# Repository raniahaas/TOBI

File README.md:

# TOBI
Telemetry, Orientation and Barometric Instrument Flight Computer used for the University of Cincinnati's Rocketry Club's Projects.\

# Introduction
TOBI, from the Japanese word 飛び（とび「tobi」）meaning to soar, was born to serve as a custom avionics bay as a foundation for the University of Cincinnati's Rocketry Club's future space attempt, as well as a custom device personally. The overall goal for final development is to have a working custom flight computer that can log data, determine events, and fire pyrotechniques, all independently.

This repository is still in _**active development**_, but is intended as a clean starting ground to learn, teach, and develop further knowledge of avionics. 

| Goals | Method(s) of Execution |
| ------------- | ------------- |
| Multithreading | Using FreeRTOS, use the two cores on the ESP32-S3 to monitor and log events while another core stores data. This became a notable issue in past iterations where often data was missed, overlapped, or entirely logged improperly. |
| Event Logging | More specifically, events for apogee, main and drogue deployment, second-stage ignition, launch, and landing. |
| Pyrotechnics | Simulate the ignition of the second stage, wire cutters, and parachute deployment that current prefab electronics for model rocketry execute. This will become a full feature later on in the following year. |
| Wi-Fi Integration | Mostly, the ESP32 is known for its Wi-Fi capabilities. In our case, I will be utilising the Wi-Fi for data transfer and to check sensor continuity. This will be the main interface that the user uses to communicate with the device externally to the development. |
| Redundancy | Logging the sensors for data and comparing their redundancy with other computers or often COTS components to ensure our code is always performing to the best of its ability while also being the best option financially and methodologically.|

## Project Structure
```
tobiru/
├── data/
│   └── assets/          
│       └── TOBI_Logo.png
├── include/
│   └── flightState.h      # Hardware headers for the flight state
├── lib/                   # Project-specific libraries
├── src/
│   ├── startup/            
|       └── imu_init.cpp   # Initialise IMU datarates
|       └── imu_init.h
|       └── startupSeq.cpp # Start device and initialise accelerometer and barometer datarates; battery voltages
|       └── startupSeq.h
│   ├── globals.h          # Global elements
|   ├── globals.cpp
│   ├── main.cpp           # Task creations
│   └── wifiSetup.h        # Web dashboard with the Wi-Fi interface
├── test/                  # Unity test suites
│   ├── test_flightstate/
|       └── test_main.cpp
│   └── test_telemetry/
|       └── test_main.cpp
└── platformio.ini
```

## Device
| Insturment | Name |
| ---------- | ---- |
| Accelerometer | [Adafruit LSM6DSO32](https://www.digikey.com/en/products/detail/adafruit-industries-llc/4692/13250946) |
| Microcontroller | [XIAO SEEED ESP32-S3](https://www.digikey.com/en/products/detail/seeed-technology-co-ltd/113991114/19285530) |
| Barometer | [TE MS5611](https://www.digikey.com/en/products/detail/te-connectivity-measurement-specialties/MS561101BA03-50/5277445) |
| PCB | See KiCAD Files |
| Mosfet | [Toshiba T2N7002](https://www.digikey.com/en/products/detail/toshiba-semiconductor-and-storage/T2N7002BK-LM/5409245) |
| Additional elements | Battery terminal, 2-prong screw terminal, 4-prong screw terminal, resistors & transistors | 

## Project Status
- [X] Create multithreaded code for sensor logging (FreeRTOS)
- [X] Have a flight state machine for pre-launch, launch, and landing
- [X] Test functions before final implementation (Unity)
- [X] Local Wi-Fi server for live telemetry data and downloading post-flight data
- [X] PCB integration testing
- [ ] Use pyrotechniques for deploying main and drogue chutes
- [ ] Test flights!

## Building and Flashing Device
The native PlatformIO extension allows the user to flash to the device by simply validating the code and 'pushing' it onto the device. 

You can additionally flash the code manually by:
```
# Build and upload firmware to the flight computer
pio run -e esp32s3 -t upload

# Open serial monitor
pio device monitor
```

## Flight State
There are three main flight states: startup, ready, and landing. Startup occurs as soon as the device is powered on and will switch to ready once all checks are complete. In the ready state, the user on the front-end server can arm and disarm the device to start recording instruments for flight. Once events are detected and landing has been determined, the device will enter landing mode and produce summary information as well as downloads for CSV files for the user. 

| State | Description |
| ----- | ----------- |
| startup |	Sensor initialization runs (runStartupSequence()), Wi-Fi starts up |
|ready |	Initialisation complete, device idle, user can access webpage |
| armed	| Event detection is live — launch/apogee/landing checks run every cycle in shutDown()|
| landed	| Landing confirmed; event detection stops, flight summary data is finalised|

Transitions are currently one-directional (no state is re-entered), driven by main.cpp on startup/arm and by the event detection logic on landing confirmation.

## Flight Events
Key flight events are detected by a pure, hardware-independent function (updateFlightState), so the same logic that flies on the device can also be validated on a laptop with no board attached.

| Event | Trigger Condition |
| ----- | ----------------- |
|Launch |	Z-axis acceleration exceeds a threshold (~15 m/s²)|
|Motor Burnout | Gs drop and at least 0.5s have passed |
|Apogee |	Altitude drops more than 50m below the recorded peak|
|Landing | Altitude returns near launch altitude, acceleration stabilises near 1G, device is stable for 3+ seconds|

## Testing
Testing is natively done with the combination of PlatformIO and Unity, where instruments are stripped, and logic functions are tested. Flight-critical logic (launch detection, apogee confirmation, landing verification) is extracted into pure, hardware-independent functions.

```
pio test -e native -f test_flightstate
```
platformio.ini defines two environments inside of testing:
- esp32s3: the physical hardware board the main code runs off of
- native: emulates real hardware to test functions purely

## Safety
This project is intended for use in HPR (high-powered rocketry) and uses pyrotechniques to deploy parachutes and allow for second-stage ignitions. All safety protocols must follow NAR safety codes and are built in accordance with a recoverable HPR two-stage flight. Do not fire, wire, or test pyrotechnic channels without knowledge of the code, device, and user-controlled testing deployment.

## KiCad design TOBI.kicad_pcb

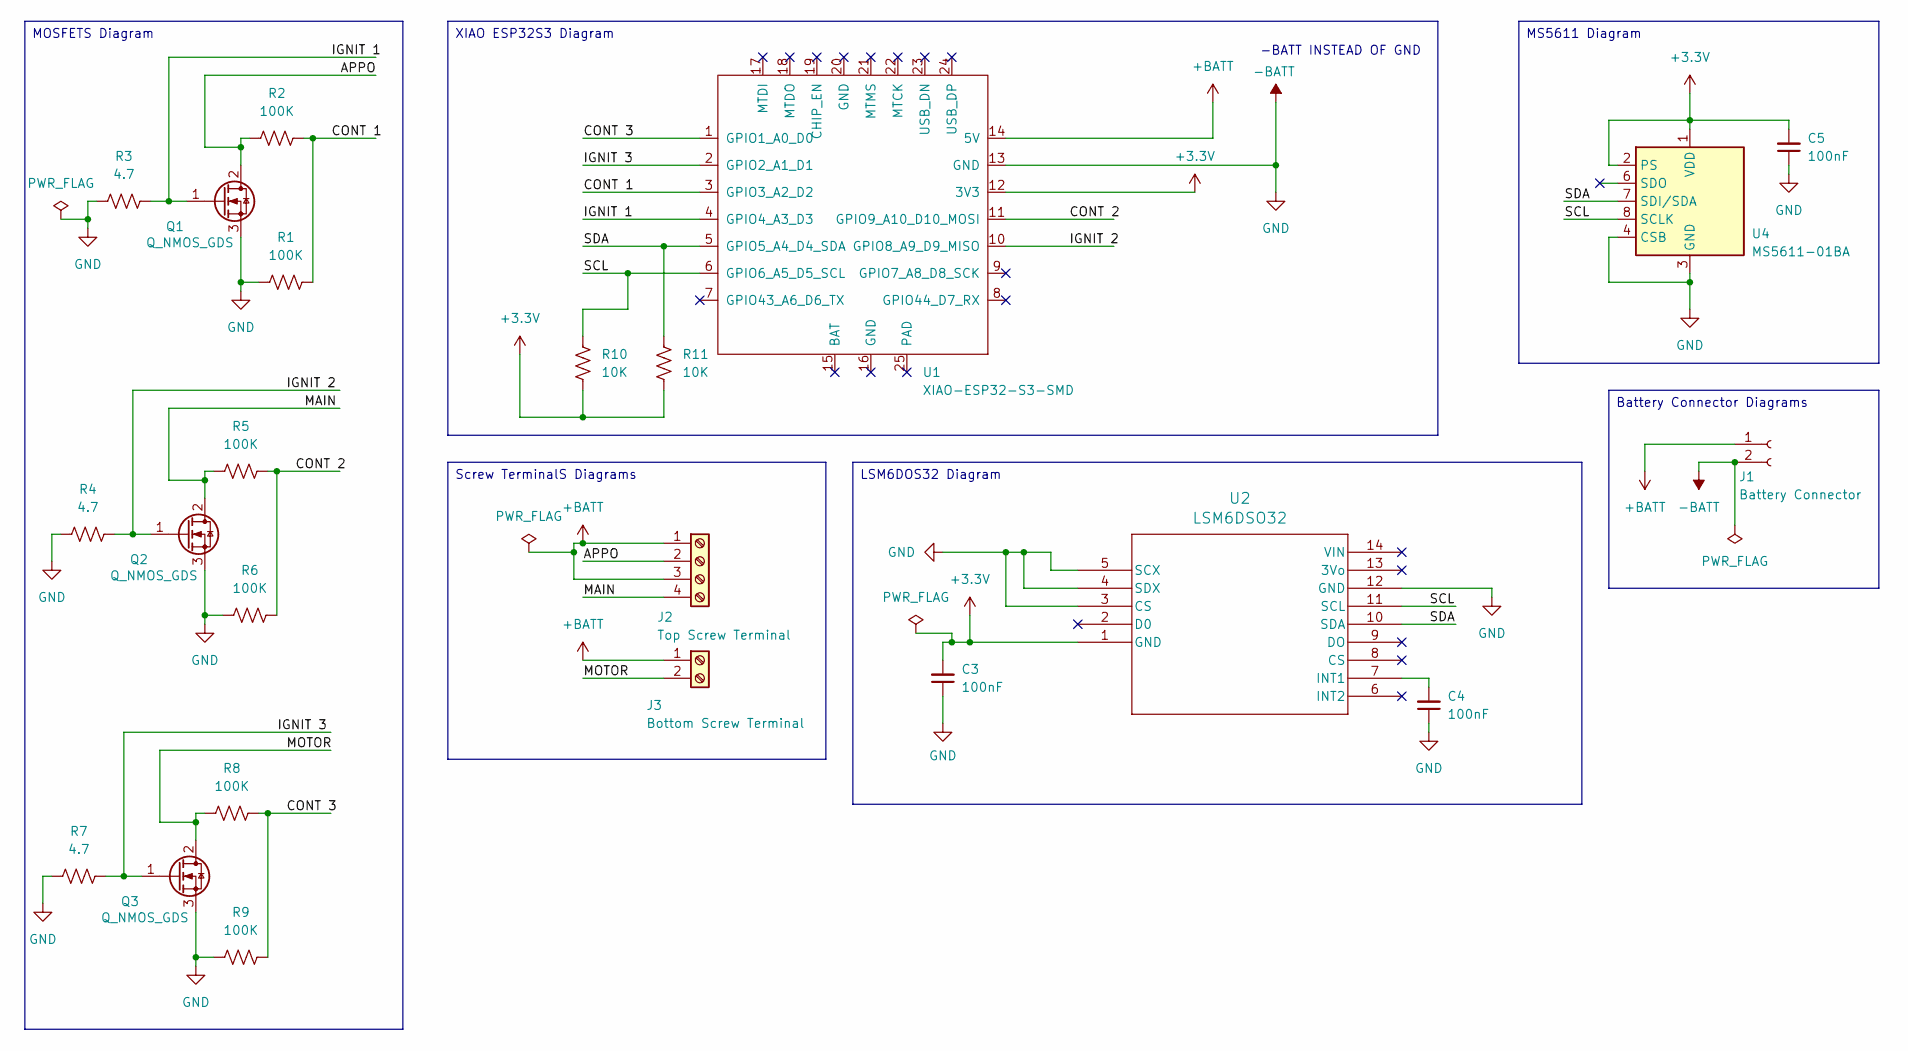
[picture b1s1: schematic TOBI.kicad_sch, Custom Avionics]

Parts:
C3, C4, C5: 100nF; C_0603_1608Metric
J1: Battery Connector; JST_PH_B2B-PH-K_1x02_P2.00mm_Vertical
J2: Top Screw Terminal; TerminalBlock_Phoenix_MPT-0,5-4-2.54_1x04_P2.54mm_Horizontal
J3: Bottom Screw Terminal; TerminalBlock_Phoenix_MPT-0,5-2-2.54_1x02_P2.54mm_Horizontal
Q1, Q2, Q3: Q_NMOS_GDS; SOT23_TOS
R1, R2, R5, R6, R8, R9: 100K; R_01005_0402Metric
R3, R4, R7: 4.7; R_01005_0402Metric
R10, R11: 10K; R_01005_0402Metric
U1: XIAO-ESP32-S3-SMD; XIAO-ESP32-S3-DIP
U2: LSM6DSO32
U4: MS5611-01BA; LGA-8_3x5mm_P1.25mm

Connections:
+3.3V: C3.2, C5.2, R10.1, R11.1, U1.12 (3V3), U2.1 (GND), U4.1 (VDD), U4.2 (PS)
+BATT: J1.1, J2.1, J2.3, J3.1, U1.14 (5V); also elsewhere on the board
-BATT: C3.1, C4.1, C5.1, J1.2, Q1.3 (S), Q2.3 (S), Q3.3 (S), R1.1, R3.1, R4.1, R6.1, R7.1, R9.1, U1.13 (GND), U2.3 (CS), U2.4 (SDX), U2.5 (SCX), U2.12 (GND), U4.3 (GND), U4.4 (CSB), U4.5 (CSB)
/APPO: J2.2, Q1.2 (D), R2.1
/CONT 1: R1.2, R2.2, U1.3 (GPIO3_A2_D2)
/CONT 2: R5.2, R6.2, U1.11 (GPIO9_A10_D10_MOSI)
/CONT 3: R8.2, R9.2, U1.1 (GPIO1_A0_D0)
/IGNIT 1: Q1.1 (G), R3.2, U1.4 (GPIO4_A3_D3)
/IGNIT 2: Q2.1 (G), R4.2, U1.10 (GPIO8_A9_D9_MISO)
/IGNIT 3: Q3.1 (G), R7.2, U1.2 (GPIO2_A1_D1)
/MAIN: J2.4, Q2.2 (D), R5.1
/MOTOR: J3.2, Q3.2 (D), R8.1; also elsewhere on the board
/SCL: R10.2, U1.6 (GPIO6_A5_D5_SCL), U2.11 (SCL), U4.8 (SCLK)
/SDA: R11.2, U1.5 (GPIO5_A4_D4_SDA), U2.10 (SDA), U4.7 (SDI/SDA)
unnamed: C4.2, U2.7 (INT1)

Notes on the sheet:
-BATT INSTEAD OF GND
XIAO ESP32S3 Diagram
MS5611 Diagram
MOSFETS Diagram
Screw TerminalS Diagrams
LSM6DOS32 Diagram
Battery Connector Diagrams

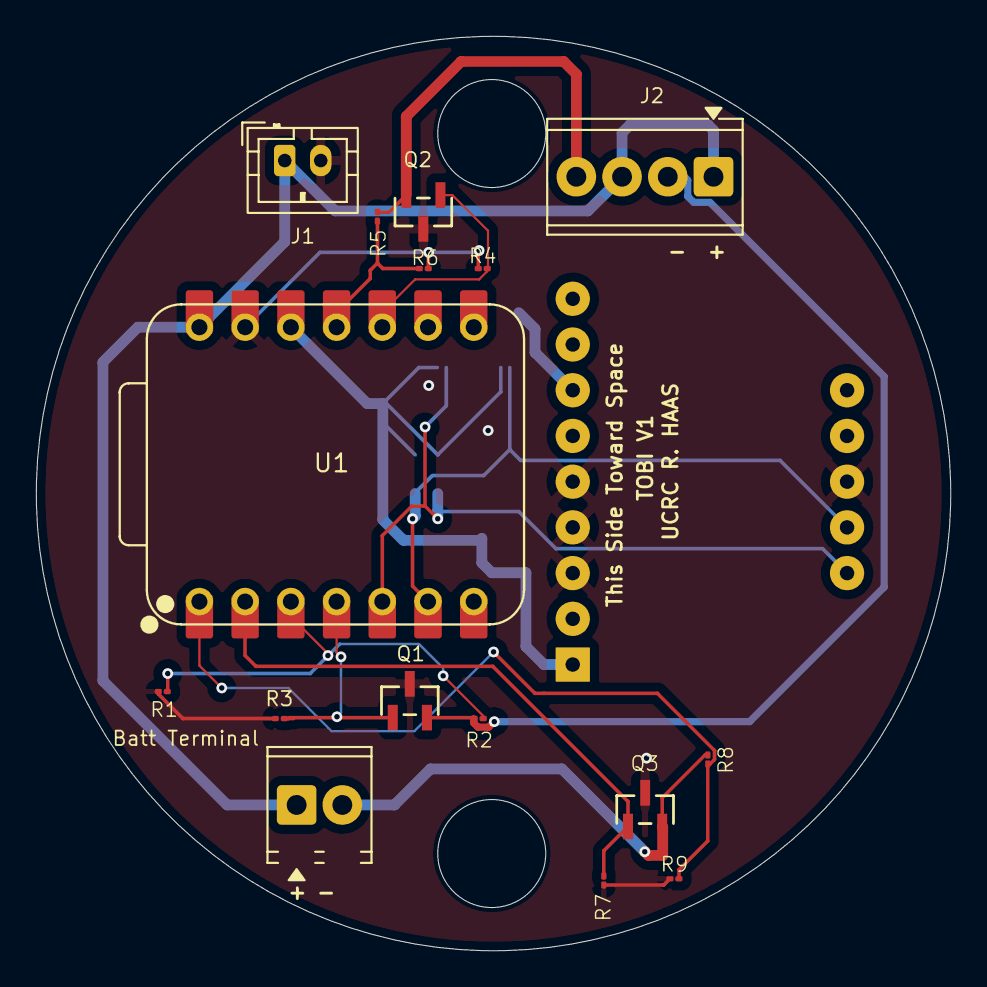
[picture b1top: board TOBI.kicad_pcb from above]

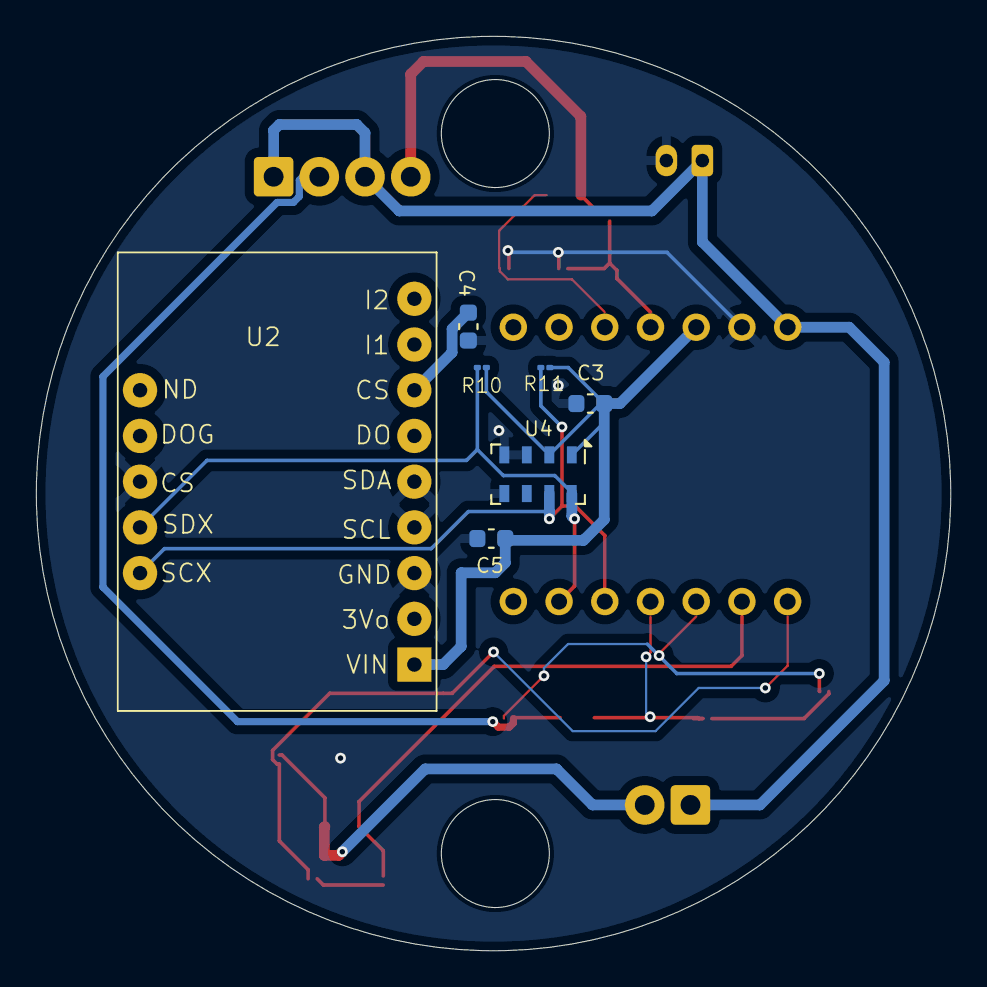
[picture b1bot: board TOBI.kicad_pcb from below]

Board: 4 copper layers, 50.8 x 50.8 mm, 23 parts (7 on the bottom side), 15 nets.

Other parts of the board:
Batt Terminal: Bottom Screw Terminal; TerminalBlock_Phoenix_MPT-0,5-2-2.54_1x02_P2.54mm_Horizontal

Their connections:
+BATT: Batt Terminal.1; also elsewhere on the board
/MOTOR: Batt Terminal.2; also elsewhere on the board

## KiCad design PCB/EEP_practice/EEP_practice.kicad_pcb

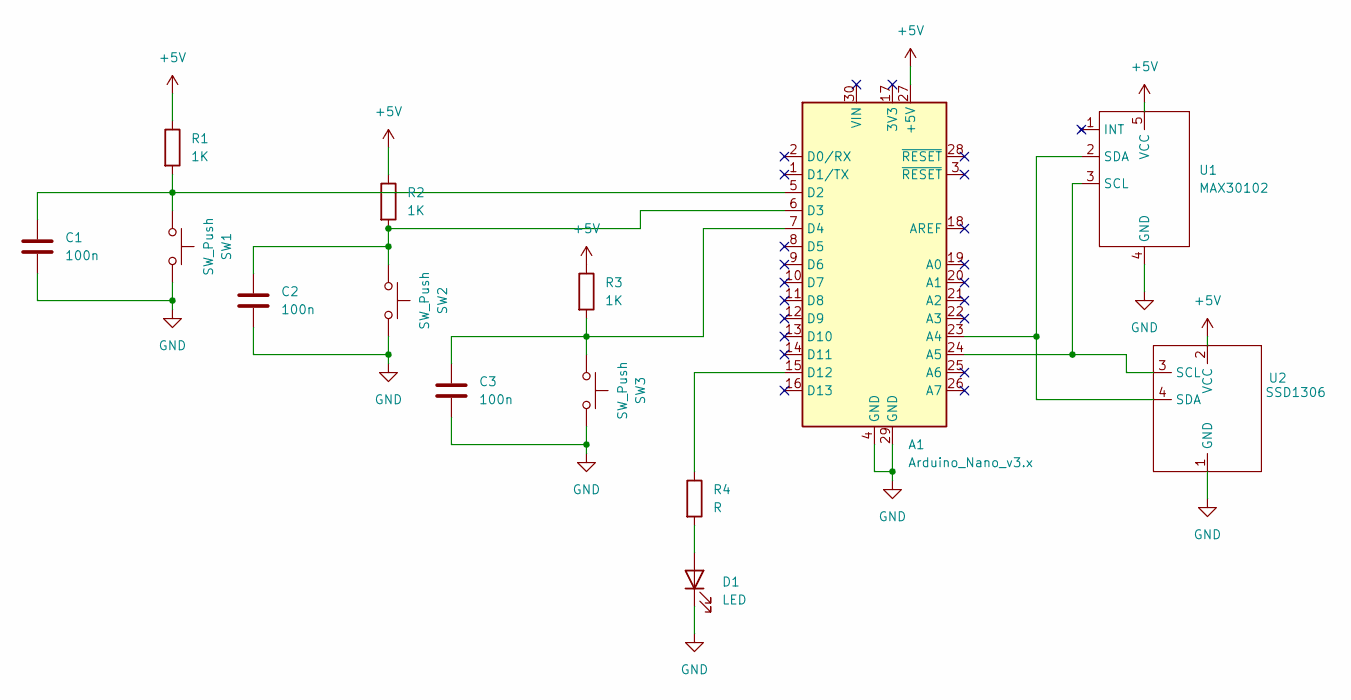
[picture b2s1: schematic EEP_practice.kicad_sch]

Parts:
A1: Arduino_Nano_v3.x; Arduino_Nano
C1, C2, C3: 100n; C_Disc_D4.7mm_W2.5mm_P5.00mm
D1: LED; LED_D5.0mm
R1, R2, R3: 1K; R_Axial_DIN0207_L6.3mm_D2.5mm_P15.24mm_Horizontal
R4: R; R_Axial_DIN0207_L6.3mm_D2.5mm_P15.24mm_Horizontal
SW1, SW2, SW3: SW_Push; SW_PUSH_6mm
U1: MAX30102; MAX30102_MODULE
U2: SSD1306

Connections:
+5V: A1.27 (+5V), R1.1, R2.1, R3.1, U1.5 (VCC), U2.2 (VCC)
GND: A1.4 (GND), A1.29 (GND), C1.2, C2.2, C3.2, D1.1 (K), SW1.2, SW2.2, SW3.2, U1.4 (GND), U2.1 (GND)
unnamed: A1.23 (A4), U1.2 (SDA), U2.4 (SDA)
unnamed: A1.24 (A5), U1.3 (SCL), U2.3 (SCL)
unnamed: A1.5 (D2), C1.1, R1.2, SW1.1
unnamed: A1.6 (D3), C2.1, R2.2, SW2.1
unnamed: A1.7 (D4), C3.1, R3.2, SW3.1
unnamed: A1.15 (D12), R4.1
unnamed: D1.2 (A), R4.2

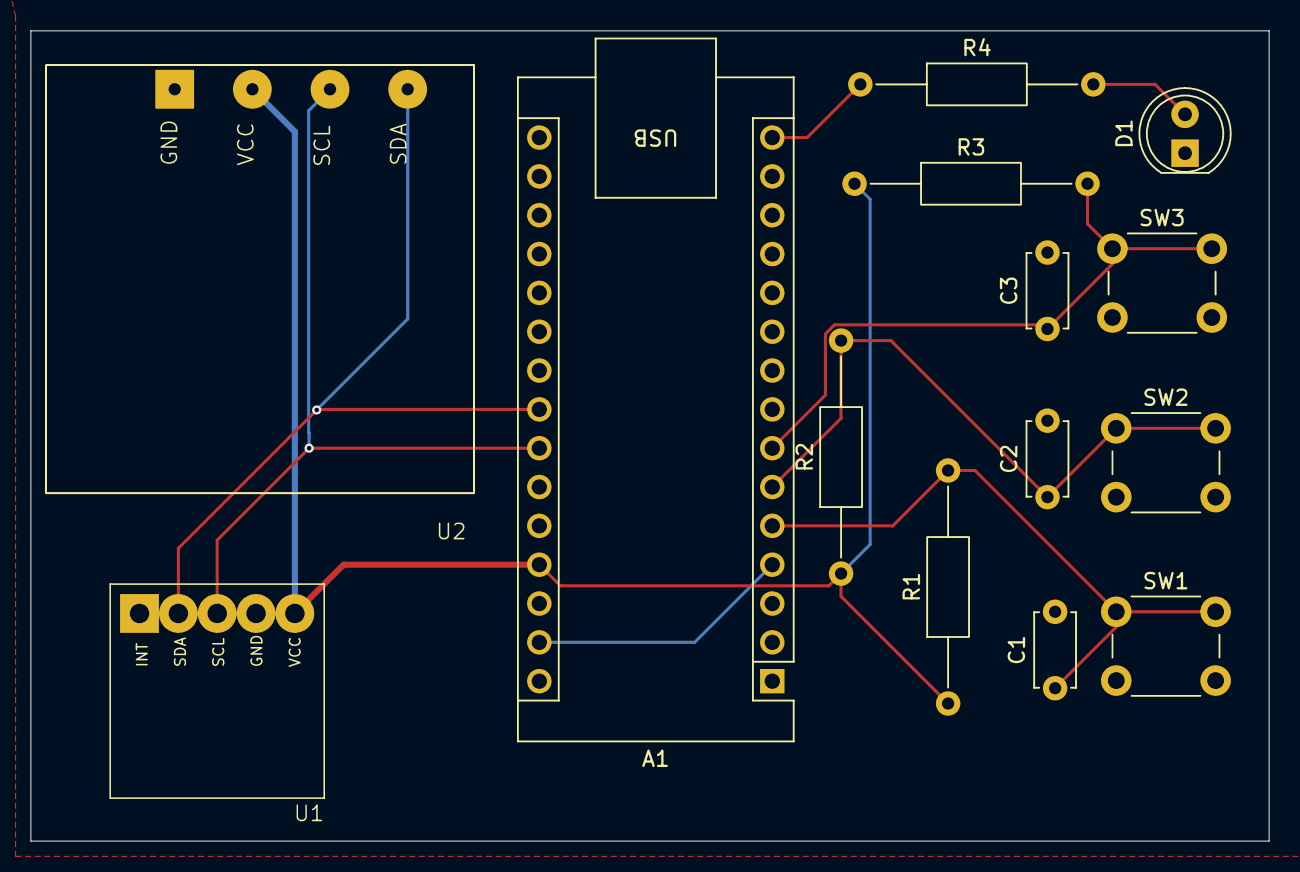
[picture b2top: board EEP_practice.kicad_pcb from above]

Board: 4 copper layers, 81.0 x 53.0 mm, 14 parts (0 on the bottom side), 9 nets.

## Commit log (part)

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2026-05-14 platformIO setup
2026-05-21 Beginnings of SOP
2026-05-21 Multithreading documentation beginnings
2026-05-22 LED Multithreading
    Simple set-up for setting multithreading up with LEDs
2026-05-22 Slate for multithreading functions
    Loop may need to be handled manually
2026-06-02 PCB practice design
    Note SOP for more information on the tutorial followed and steps of completion.
2026-06-03 Basic for PCB Design
    Included all current parts for PCB schematics, preparing parts for PCB board design.
2026-06-03 Function declaration fix
    Properly instantiated the RTOS threading requirements
2026-06-03 Start-up
    Initial makeup of init files for dso32
2026-06-05 Final Schematics
    Checked schematics and parts
2026-06-14 IMU Init
    Initial checks for IMU startup dso32, code clear untested with physical device
2026-06-14 Voltage Checks
    Check battery voltage and ensure device is safe to move forward. This is an additional check done by the computer this should be completed by hand with a multimeter before launch. Untested with batte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
2026-06-15 PCB Layout Design I
    First design for PCB: current concerns include the soldering distance and the current state of the rats nest--possibly too many vias?
2026-06-16 IMU Testing
    Tests for IMU, inside of the setup loop currently all checks are running however when then placed in the core it is dumping. Saving for reference.
2026-06-16 Finished IMU Checks
    IMU checks are currently running, since we are only calling startup once, it was moved to a separate file rather than as a core event; most likely will do a similar idea when it comes to shutdown
2026-06-17 Updated Battery Checks
    Current battery checks are running and working properly when plugged into a computer. This will become more important information and of a check when the webserver is created.
2026-06-17 Final initial threading setup
    Small changes and serial print lines before rebasing and closing ticket
2026-06-18 PCB Design Fixes from Andrew
    Meeting notes: PCB design considerations:
    Can go a hair bigger on track width with the smaller pads; 0.5/0.6
    Front:
    Make the trace around the threaded rod more of a 45º than 90º
    Middle
    Go through the middle rather than around the bend
2026-06-18 More beginning WiFi work
    Placeholder sections for body and 404 pages
2026-06-24 TOBI Logo
    Added TOBI logo PNG for HTML server
2026-06-24 Modified ESP32S3 Footprint
    Incorrect footprint for the ESP, updated and modified the PCB for re-wiring.
2026-06-25 Updated Wiring
    Semi-final wiring for PCB.
2026-06-25 Silkscreen Text Modifications
    Added more descriptive text, edited sizes for labeling, as well as general board info text.
2026-06-26 Final PCB
    Final PCB that is being pushed out, DRC checks fine
2026-06-26 Additional Final Changes for Gerber
    Little tweaks for threaded rod holes, version pushed to JLC PBC.
2026-06-30 Initial WiFi Setup for main
    Added full HTML file without integration into wifisetup.h as well as integrated with main to allow and start the WiFi server on the ESP.
